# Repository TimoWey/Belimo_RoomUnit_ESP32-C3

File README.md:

# Belimo RoomUnit ESP32-C3

This project reads Temperature, Humidity, and CO2 levels from a Belimo Room Unit sensor using a Seeed XIAO ESP32-C3 and publishes the data via MQTT.

## Hardware Requirements

- Seeed XIAO ESP32-C3 board (https://wiki.seeedstudio.com/XIAO_ESP32C3_Getting_Started/)
- Belimo Room Unit sensor
- Power supply (USB or external)
- Connecting wires

## Wiring

Connect the Belimo Room Unit to the ESP32-C3 as follows:

| Belimo Signal | ESP32-C3 Pin | ADC Channel |
|---------------|--------------|-------------|
| Temperature   | GPIO2/A2     | ADC2        |
| Humidity      | GPIO3/A3     | ADC3        |
| CO2           | GPIO4/A4     | ADC4        |
| GND           | GND          | -           |

## Software Setup

### Prerequisites

1. Install ESP-IDF (Espressif IoT Development Framework)
2. Clone this repository
3. Navigate to the project directory

### Configuration

1. Configure the WiFi and other project settings using:
```bash
idf.py menuconfig
```

Under "Example Configuration":
- Set WiFi SSID
- Set WiFi Password

2. Update the following parameters in `main/main.c` according to your setup:
```c
#define MQTT_BROKER_URL "mqtt://192.168.0.68"    // Your MQTT broker IP/hostname
#define MQTT_PORT 1883                           // Your MQTT broker port
#define MQTT_TOPIC_TEMP "sensors/temperature_2"  // MQTT topic for temperature
#define MQTT_TOPIC_HUMIDITY "sensors/humidity_2" // MQTT topic for humidity
#define MQTT_TOPIC_CO2 "sensors/co2_2"          // MQTT topic for CO2
```

3. Optional settings you can modify:
- `LED_BLINK_ENABLED`: Set to `true` to enable status LED blinking
- `FILTER_SIZE`: Number of samples for reading averaging (default: 16)
- `SAMPLE_INTERVAL`: Time between samples in ms (default: 100)

4. Flash to your device:

```bash
idf.py -p [PORT] flash
```
```bash
idf.py monitor
```

## MQTT Data Format

The device publishes JSON data to three topics:

1. Temperature (sensors/temperature):

```json
{"voltage": 1.23, "temperature": 24.5}
```

2. Humidity (sensors/humidity):

```json
{"voltage": 1.23, "humidity": 50.0}
```

3. CO2 (sensors/co2):

```json
{"voltage": 1.45, "humidity": 45.2}
```

{"voltage": 1.67, "co2": 850.0}

## Sensor Ranges

- Temperature: 0°C to 50°C
- Humidity: 0% to 100%
- CO2: 0 to 2000 ppm

## LED Indicator

The onboard LED (GPIO10) can be enabled for status indication by setting `LED_BLINK_ENABLED` to `true` in the code.

## Troubleshooting

1. If the device fails to connect to WiFi:
   - Check your WiFi credentials
   - Ensure the device is within range of your WiFi network
   - Monitor the serial output for connection status

2. If MQTT publishing fails:
   - Verify your MQTT broker is running
   - Check the broker URL and port
   - Ensure your network allows MQTT traffic

## License

This project is open-source and available under the MIT License.

## Contributing

Feel free to submit issues and pull requests to improve this project.

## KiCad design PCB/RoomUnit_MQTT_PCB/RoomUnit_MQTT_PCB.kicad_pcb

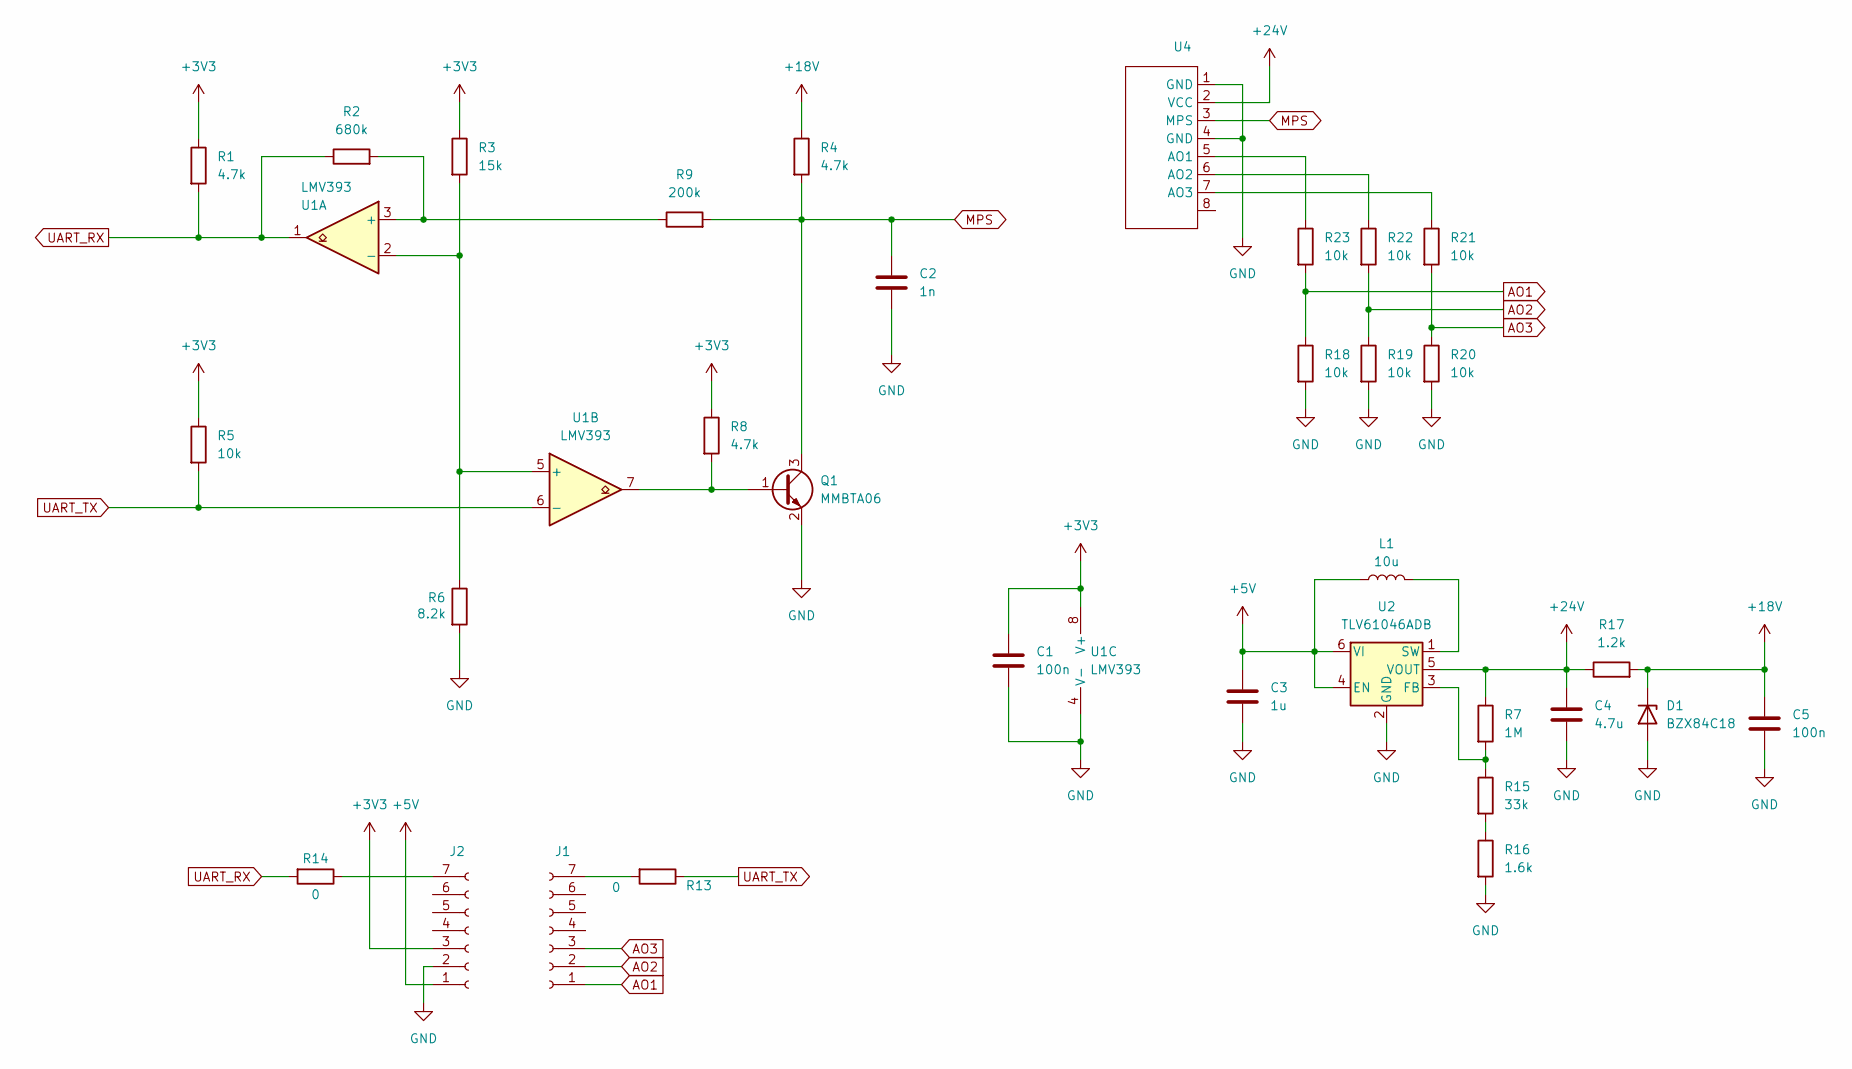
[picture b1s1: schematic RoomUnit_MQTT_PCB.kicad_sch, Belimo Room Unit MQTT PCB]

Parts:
C1, C5: 100n; C_0805_2012Metric_Pad1.18x1.45mm_HandSolder
C2: 1n; C_0805_2012Metric_Pad1.18x1.45mm_HandSolder
C3: 1u; C_1206_3216Metric
C4: 4.7u; C_1206_3216Metric
D1: BZX84C18; SOT-23
J1, J2: Conn_01x07_Socket; XIAO_ESP32-C3_Custom_Connector
L1: 10u; L_Chilisin_BMRA00040420
Q1: MMBTA06; SOT-23
R1, R4, R8: 4.7k; R_0805_2012Metric_Pad1.20x1.40mm_HandSolder
R2: 680k; R_0805_2012Metric_Pad1.20x1.40mm_HandSolder
R3: 15k; R_0805_2012Metric_Pad1.20x1.40mm_HandSolder
R5, R18, R19, R20, R21, R22, R23: 10k; R_0805_2012Metric_Pad1.20x1.40mm_HandSolder
R6: 8.2k; R_0805_2012Metric_Pad1.20x1.40mm_HandSolder
R7: 1M; R_0805_2012Metric_Pad1.20x1.40mm_HandSolder
R9: 200k; R_0805_2012Metric_Pad1.20x1.40mm_HandSolder
R13, R14: 0; R_0805_2012Metric_Pad1.20x1.40mm_HandSolder
R15: 33k; R_0805_2012Metric_Pad1.20x1.40mm_HandSolder
R16: 1.6k; R_0805_2012Metric_Pad1.20x1.40mm_HandSolder
R17: 1.2k; R_0805_2012Metric_Pad1.20x1.40mm_HandSolder
U1: LMV393; SOIC-8_3.9x4.9mm_P1.27mm
U2: TLV61046ADB; SOT-23-6
U4: RoomUnit_Connector_5mm

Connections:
+3V3: C1.1, J2.3, R1.1, R3.1, R5.1, R8.1, U1.8 (V+)
+5V: C3.1, J2.1, L1.1, U2.4 (EN), U2.6 (VI)
+18V: C5.1, D1.3 (K), R4.1, R17.2
+24V: C4.1, R7.1, R17.1, U2.5 (VOUT), U4.2 (VCC)
AO1: J1.1, R18.1, R23.2
AO2: J1.2, R19.1, R22.2
AO3: J1.3, R20.1, R21.2
GND: C1.2, C2.2, C3.2, C4.2, C5.2, D1.1 (A), J2.2, Q1.2 (E), R6.2, R16.2, R18.2, R19.2, R20.2, U1.4 (V-), U2.2 (GND), U4.1 (GND), U4.4 (GND)
MPS: C2.1, Q1.3 (C), R4.2, R9.2, U4.3 (MPS)
unnamed: J1.7, R13.2
unnamed: J2.7, R14.1
unnamed: Q1.1 (B), R8.2, U1.7
unnamed: R15.2, R16.1
unnamed: R2.2, R9.1, U1.3 (+)
unnamed: R3.2, R6.1, U1.2 (-), U1.5 (+)
unnamed: R7.2, R15.1, U2.3 (FB)
unnamed: L1.2, U2.1 (SW)
unnamed: R23.1, U4.5 (AO1)
unnamed: R22.1, U4.6 (AO2)
unnamed: R21.1, U4.7 (AO3)
UART_RX: R1.2, R2.1, R14.2, U1.1
UART_TX: R5.2, R13.1, U1.6 (-)

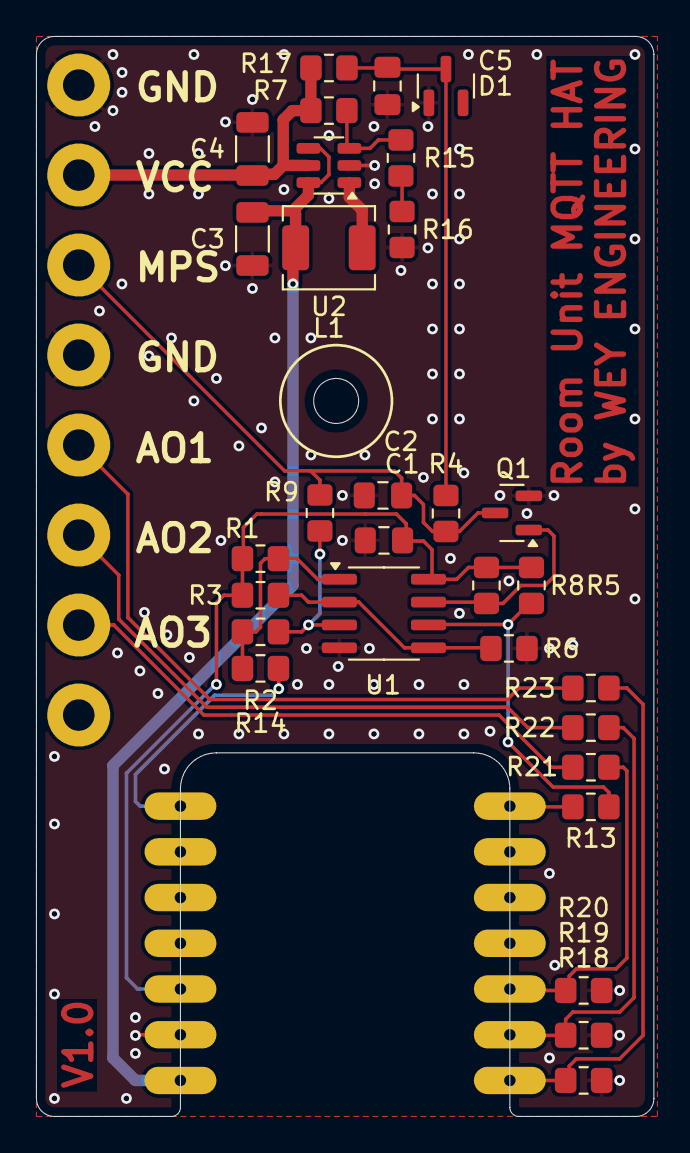
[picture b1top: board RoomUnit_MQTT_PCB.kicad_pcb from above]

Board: 2 copper layers, 34.3 x 60.0 mm, 33 parts (0 on the bottom side), 22 nets.

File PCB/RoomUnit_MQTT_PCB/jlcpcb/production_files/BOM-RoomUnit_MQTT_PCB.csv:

Comment,Designator,Footprint,LCSC,Quantity
1M,R7,R_0805_2012Metric_Pad1.20x1.40mm_HandSolder,C107700,1
200k,R9,R_0805_2012Metric_Pad1.20x1.40mm_HandSolder,C114562,1
10u,L1,L_Chilisin_BMRA00040420,C133195,1
8.2k,R6,R_0805_2012Metric_Pad1.20x1.40mm_HandSolder,C137399,1
1.6k,R16,R_0805_2012Metric_Pad1.20x1.40mm_HandSolder,C137580,1
33k,R15,R_0805_2012Metric_Pad1.20x1.40mm_HandSolder,C141696,1
1n,C2,C_0805_2012Metric_Pad1.18x1.45mm_HandSolder,C15177,1
1.2k,R17,R_0805_2012Metric_Pad1.20x1.40mm_HandSolder,C17379,1
10k,"R21,R22,R23,R5",R_0805_2012Metric_Pad1.20x1.40mm_HandSolder,C17414,4
15k,R3,R_0805_2012Metric_Pad1.20x1.40mm_HandSolder,C17475,1
0,"R13,R14",R_0805_2012Metric_Pad1.20x1.40mm_HandSolder,C17477,2
4.7k,"R1,R4,R8",R_0805_2012Metric_Pad1.20x1.40mm_HandSolder,C17673,3
680k,R2,R_0805_2012Metric_Pad1.20x1.40mm_HandSolder,C17797,1
1u,C3,C_1206_3216Metric,C1848,1
BZX84C18,D1,SOT-23,C19077473,1
MMBTA06,Q1,SOT-23,C20069139,1
100n,"C1,C5",C_0805_2012Metric_Pad1.18x1.45mm_HandSolder,C28233,2
4.7u,C4,C_1206_3216Metric,C29823,1
TLV61046ADB,U2,SOT-23-6,C464815,1
LMV393,U1,SOIC-8_3.9x4.9mm_P1.27mm,C7984,1

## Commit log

2025-01-16 Initial Commit - Blink Script works!
2025-01-16 reads temperature via ADC
2025-01-16 publishing via mqtt
2025-01-18 now reading temp, hum and co2
2025-02-17 fixed some errors - code beautify
2025-02-17 removed default state logging mqtt
2025-02-17 Squashed commit of the following:
    commit c27bc66c1dc90af4e393e254ebacadaf945d637d
    Author: Timää <timo@ritawey.ch>
    Date: Mon Feb 17 20:25:50 2025 +0100
    removed default state logging mqtt
    commit 88ae49d116315932d22b60c2f9d53f3f696779f4
    Author: Timää <timo@ritawey.ch>
2025-02-17 readme esp32 link added
2025-03-08 3D PCB Print 1
2025-03-08 Cleanup
2025-03-09 PCB outline done
2025-03-09 pcb progress
2025-03-09 pcb export
2025-03-12 Von Stefan korrigierte Version
2025-03-12 applied schematic changes (wip)
2025-03-12 PCB improvements
2025-03-13 schematic updated 18V
2025-03-13 SChematic update - PCB almost done
2025-03-13 added all jlc components
2025-03-15 Spannungsteiler AOx
2025-03-15 3D assembly
2025-03-15 DRC passed
2025-03-15 fixed placement and package
2025-03-15 Ordered
